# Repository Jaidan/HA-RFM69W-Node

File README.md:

# Wireless Home Automation Node

See the following link for Arduino drivers for the RFM69W  
  * https://github.com/LowPowerLab/RFM69

## Order PCBs  

You can order this PCB directly from OSH Park.  Click on the following link.  
  * https://oshpark.com/shared_projects/0tyMCEgR

See Bill of Materials file in repo for parts list.  

## Status  
  * PCB layout is currently untested.   

## File Formats  

Design files are in "CadSoft EAGLE PCB Design Software" .brd and .sch formats.  
A free version of the software can be downloaded from www.cadsoftusa.com.  

## Attribution

ALl credit for the original layout from which this is based goes to https://github.com/uChip/RFM69W_BOB

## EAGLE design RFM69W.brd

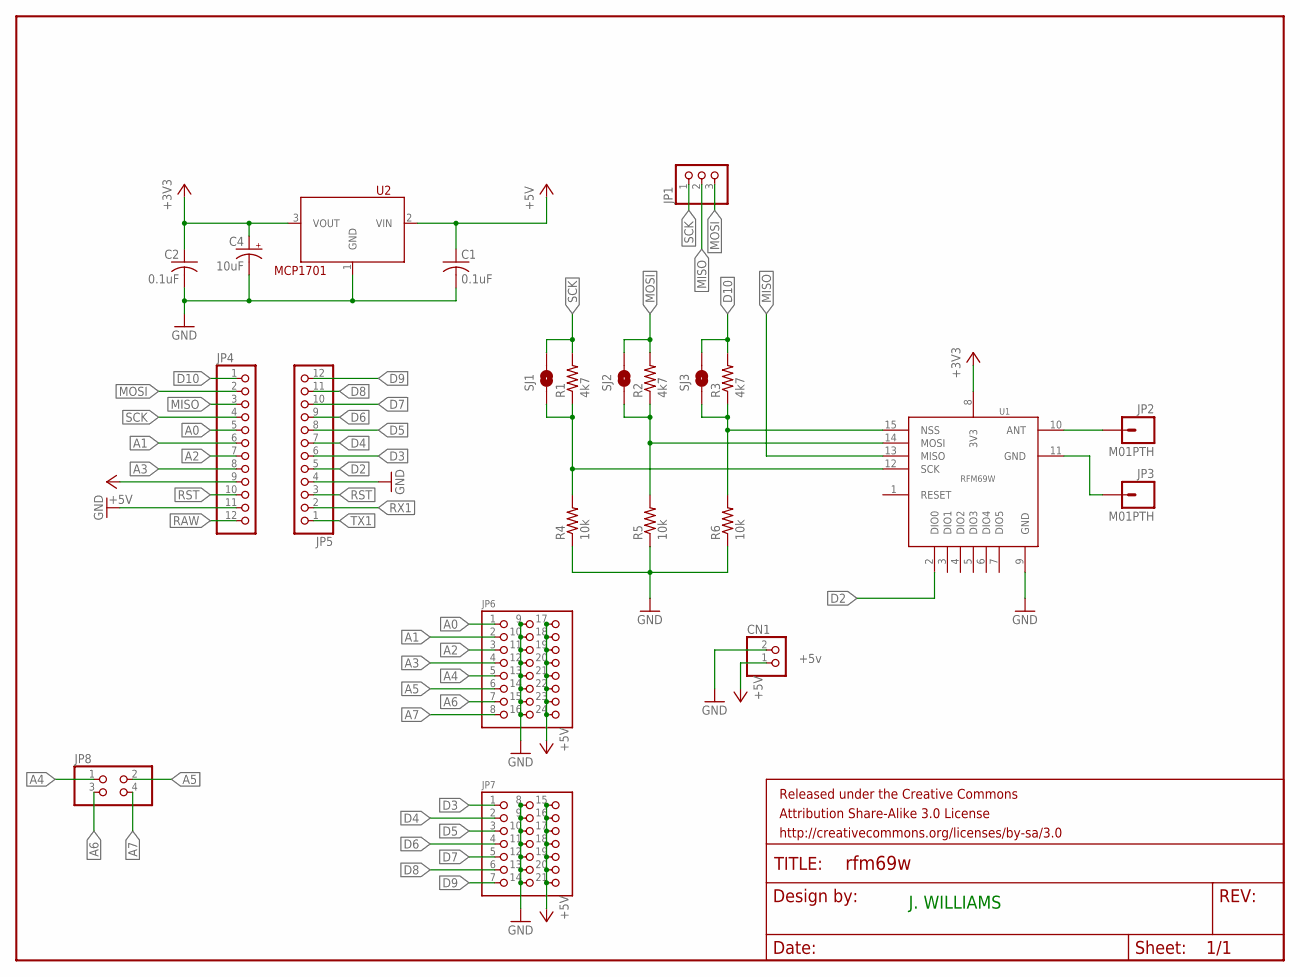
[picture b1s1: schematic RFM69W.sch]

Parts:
C1, C2: 0.1uF; C1206
C4: 10uF; A/3216-18R
CN1: +5v; JST-PH-2-THM-RA
FRAME1: FRAME-LETTER; CREATIVE_COMMONS
JP1: PINHD-1X3; 1X03
JP2, JP3: M01PTH; 1X01
JP4, JP5: PINHD-1X12; 1X12
JP6: PIN_3X8
JP7: PIN_3X7
JP8: PINHD-2X2; 2X02
R1, R2, R3: 4k7; R1206
R4, R5, R6: 10k; R1206
SJ1, SJ2, SJ3: SOLDERJUMPERNO; SJ_2S-NO
U1: RFM69W
U2: MCP1701; SOT-89

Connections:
+3V3: C2.1, C4.+, U1.8 (3V3), U2.3 (VOUT)
+5V: C1.1, CN1.1 (2), JP4.9, JP6.17, JP6.18, JP6.19, JP6.20, JP6.21, JP6.22, JP6.23, JP6.24, JP7.15, JP7.16, JP7.17, JP7.18, JP7.19, JP7.20, JP7.21, U2.2 (VIN)
A0: JP4.5, JP6.1
A1: JP4.6, JP6.2
A2: JP4.7, JP6.3
A3: JP4.8, JP6.4
A4: JP6.5, JP8.1
A5: JP6.6, JP8.2
A6: JP6.7, JP8.3
A7: JP6.8, JP8.4
D2: JP5.5, U1.2 (DIO0)
D3: JP5.6, JP7.1
D4: JP5.7, JP7.2
D5: JP5.8, JP7.3
D6: JP5.9, JP7.4
D7: JP5.10, JP7.5
D8: JP5.11, JP7.6
D9: JP5.12, JP7.7
D10: JP4.1, R3.2, SJ3.2
GND: C1.2, C2.2, C4.-, CN1.2 (1), JP4.11, JP5.4, JP6.9, JP6.10, JP6.11, JP6.12, JP6.13, JP6.14, JP6.15, JP6.16, JP7.8, JP7.9, JP7.10, JP7.11, JP7.12, JP7.13, JP7.14, R4.1, R5.1, R6.1, U1.9 (GND), U2.1 (GND)
MISO: JP1.2, JP4.3, U1.13 (MISO)
MOSI: JP1.3, JP4.2, R2.2, SJ2.2
unnamed: R3.1, R6.2, SJ3.1, U1.15 (NSS)
unnamed: R2.1, R5.2, SJ2.1, U1.14 (MOSI)
unnamed: R1.1, R4.2, SJ1.1, U1.12 (SCK)
unnamed: JP2.1, U1.10 (ANT)
unnamed: JP3.1, U1.11 (GND)
RAW: JP4.12
RST: JP4.10, JP5.3
RX1: JP5.2
SCK: JP1.1, JP4.4, R1.2, SJ1.2
TX1: JP5.1

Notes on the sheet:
J. WILLIAMS

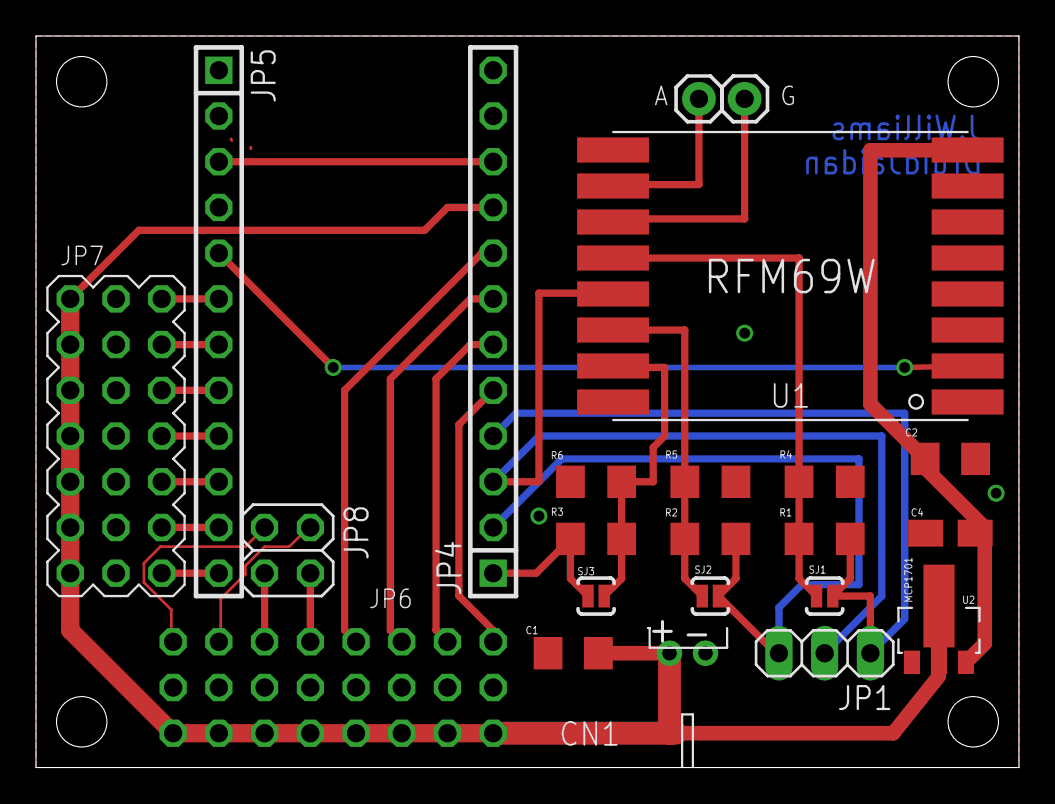
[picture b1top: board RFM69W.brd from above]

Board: 2 copper layers, 54.6 x 40.6 mm, 24 parts (1 on the bottom side), 29 nets.

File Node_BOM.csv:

"Part";"Value";"Device";"Package";"Description";"";
"C1";"0.1uF";"C-USC1206";"C1206";"CAPACITOR, American symbol";"";
"C2";"0.1uF";"C-USC1206";"C1206";"CAPACITOR, American symbol";"";
"C4";"10uF";"CPOL-USA/3216-18R";"A/3216-18R";"POLARIZED CAPACITOR, American symbol";"";
"CN1";"+5v";"JST_2PIN-THM-RA";"JST-PH-2-THM-RA";"JST 2-Pin Connectors of various flavors";"";
"FRAME1";"FRAME-LETTER";"FRAME-LETTER";"CREATIVE_COMMONS";"Schematic Frame";"";
"JP1";"";"PINHD-1X3";"1X03";"PIN HEADER";"";
"JP2";"M01PTH";"M01PTH";"1X01";"Header 1";"";
"JP3";"M01PTH";"M01PTH";"1X01";"Header 1";"";
"JP4";"";"PINHD-1X12";"1X12";"PIN HEADER";"";
"JP5";"";"PINHD-1X12";"1X12";"PIN HEADER";"";
"JP6";"PIN_3X8";"PIN_3X8";"PIN_3X8";"";"";
"JP7";"PIN_3X7";"PIN_3X7";"PIN_3X7";"";"";
"JP8";"";"PINHD-2X2";"2X02";"PIN HEADER";"";
"R1";"4k7";"R-US_R1206";"R1206";"RESISTOR, American symbol";"";
"R2";"4k7";"R-US_R1206";"R1206";"RESISTOR, American symbol";"";
"R3";"4k7";"R-US_R1206";"R1206";"RESISTOR, American symbol";"";
"R4";"10k";"R-US_R1206";"R1206";"RESISTOR, American symbol";"";
"R5";"10k";"R-US_R1206";"R1206";"RESISTOR, American symbol";"";
"R6";"10k";"R-US_R1206";"R1206";"RESISTOR, American symbol";"";
"SJ1";"";"SOLDERJUMPERNO";"SJ_2S-NO";"Solder Jumper";"";
"SJ2";"";"SOLDERJUMPERNO";"SJ_2S-NO";"Solder Jumper";"";
"SJ3";"";"SOLDERJUMPERNO";"SJ_2S-NO";"Solder Jumper";"";
"U1";"RFM69W";"RFM69W";"RFM69W";"Radio Transceiver Module, FSK, 433, 848, 915 MHz, SPI controlled, Mfr=HopeRF";"";
"U2";"MCP1701";"MCP1701";"SOT-89";"Voltage Regulator, LDO, fixed 1.8,2.5,3.0,3.3,5.0V, 500mW/Vdrop";"";

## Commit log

2015-04-16 Combo Arduino Pro Mini and RFM69W
2015-04-16 Add image and README updates
2015-04-16 Add copy od LICENSE
2015-04-16 Image fix
2015-04-16 Semicolon separators are silly

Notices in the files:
parts and their libraries:
SparkFun-Aesthetics: Licensing: CC v3.0 Share-Alike You are welcome to use this library for commercial purposes.
SparkFun-Aesthetics: Released under the Creative Commons Attribution Share-Alike 3.0 License
SparkFun-Aesthetics: http://creativecommons.org/licenses/by-sa/3.0
